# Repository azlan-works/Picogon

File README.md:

# Picogon
The Picogon in an opensource RP2354A based board for compact embedded applications. Designed as a host platform to integrate with more complex use cases, with peripherals attachable via exposed ENIG pads that connect to spring contacts on a compatible daughterboard. 

## Features:

- USB-C PD/PPS (3.3V to 24V)
- Battery management (3.7V LiPo)
- WiFi/BLE (2.4GHz built-in antenna)
- LoRa (SX1262 868-915MHz UFL connector)
- 9-axis DoF (IMU + Magnetometer)
- QWIIC/Stemma I2C port

  ## Notes:
  Currently untested

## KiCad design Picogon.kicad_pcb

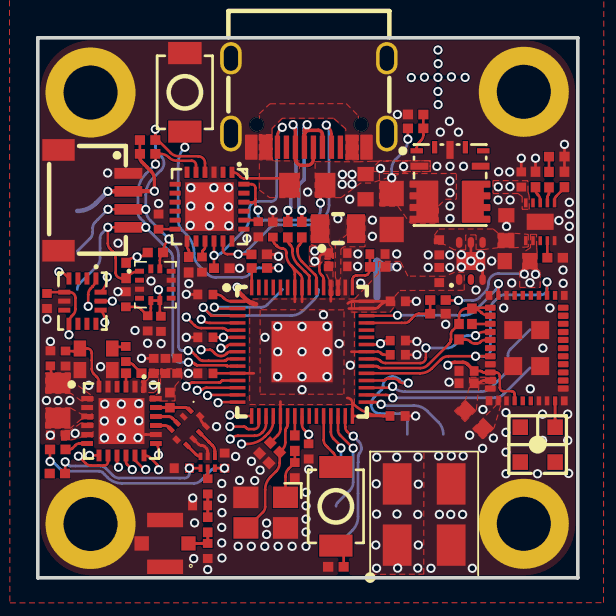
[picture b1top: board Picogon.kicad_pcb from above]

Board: 6 copper layers, 30.0 x 30.0 mm, 100 parts (0 on the bottom side), 75 nets.

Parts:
AE1: 47948-0001; ANT-SMD_47948-0001
C1, C11, C21, C22: 4.7uF; C0402
C2, C3, C4, C5, C6, C7, C8, C9, C10, C26, C27, C29, C30, C31, C33, C36, C37: 100nF; C0402
C12, C13: 4.7uF; C0402_WIDE
C14, C15: 15pF; C0402
C16: 47uF; C0805
C17: 10uF; C0603
C18: 10uF; C0402
C19, C23: 22uF; C0603
C20, C24, C25, C28, C35: 1uF; C0402
C32: 10pF; C0402
C34: 470nF; C0402
C38: 47pF; C0402
C39: 39pF; C0402
C40, C41: 33pF; C0402
C42, C43: 3.9pF; C0402
CN1: QWIIC; CONN-SMD_4P-P1.00_SM04B-SRSS-TB-LF-SN
L1: 3.3uH; IND-SMD_L2.0-W1.6_AOTA-B201610S3R3-101-T
L2: 2.2uH; L0603
L3: 10uH; L0805
L4: 47nH; L0402
L5: 9.1nH; L0402
M1, M2, M3, M4: M3_Hole
M5: 0900FM15K0039001E; FILTER-SMD_10P-L2.0-W1.3-BL
R1: 33Ω; R0402
R2, R3, R6: 1kΩ; R0402
R4, R5: 27Ω; R0402
R7, R10, R13, R16, R17, R20, R21: 10kΩ; R0402
R8, R9, R26, R27: 4.7kΩ; R0402
R11: 470Ω; R0402
R12: 1.5kΩ; R0402
R14: 3.3kΩ; R0402
R15, R18: 220Ω; R0402
R19, R29: 100Ω; R0402
R22: 10mΩ; R0805
R23, R24: 5.1kΩ; R0402
R25: 10kΩ; R0402
R28: FM8625H; DFN-6_L1.1-W0.7-P0.40-BL
SW1, SW2: Button; SW-SMD_L3.9-W3.0-P4.45
TCXO1: 32MHz; OSC-SMD_4P-L2.0-W1.6-BL_1XXD
U1: RP2354A; QFN-60_L7.0-W7.0-P0.40-TL-EP3.4
U2: ABM8-272-T3; CRYSTAL-SMD_4P-L3.2-W2.5-BL
U3: TPSM84209RKHR; QFN-9_L4.5-W4.0_TPSM84209RKHR
U4: ICM-42688-P; LGA-14_L3.0-W2.5-P0.50-TL
U5: LBEE5KL1YN-814; LGA-46_L7.0-W5.2_LBEE5KL1DX-883
U6: BQ25185DLHR; WSON-10_L2.2-W2.0-P0.40-BL-EP_TI_DLH0010A
U7: TLV76733DRVR; WSON-6_L2.0-W2.0-P0.65-TL-EP
U8: AP33772DKZ-13; QFN-24_L4.0-W4.0-P0.50-TL-EP2.7
U9: LIS3MDLTR; LGA-12_L2.0-W2.0-P0.50-BL
U10: SX1262IMLTRT; QFN-24_L4.0-W4.0-P0.50-BL-EP2.6
U11: IPEX-1; IPEX-SMD_4P-L2.6-W2.6-LS3.0
U12: 009296002202906; CONN-SMD_009296002202906
USBC1: USB-C 16P; USB-C_SMD-TYPE-C-31-M-12_1

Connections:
+1V1: C1.2, C2.2, C3.2, C13.2, L1.2, U1.6 (DVDD), U1.23 (DVDD), U1.39 (DVDD), U1.50 (VREG_FB)
+3V3: C4.2, C5.2, C6.2, C7.2, C8.2, C9.2, C10.2, C12.2, C20.2, C21.2, C25.2, C29.2, C30.2, C31.2, C35.2, C36.2, CN1.2 (VCC), R1.1, R8.2, R9.2, R26.2, R27.2, U1.1 (IOVDD), U1.11 (IOVDD), U1.20 (IOVDD), U1.30 (IOVDD), U1.38 (IOVDD), U1.44 (ADC_AVDD), U1.45 (IOVDD), U1.49 (VREG_VIN), U1.53 (USB_OTP_VDD), U1.54 (QSPI_IOVDD), U4.5 (VDDIO), U4.8 (VDD), U5.30 (VBAT), U5.36 (VIO), U7.1 (OUT), U9.5 (Vdd), U9.6 (Vdd_IO), U10.1 (VDD_IN), U10.10 (VBAT), U10.11 (VBAT_IO)
+BATT: C23.2, R20.2, U6.2 (BAT), U12.1
/Power/BAT_ADC: R20.1, R21.2, U1.42 (GPIO28_ADC2)
/Power/CC1: R23.2, U8.17 (CC1), USBC1.A5 (CC1)
/Power/CC2: R24.2, U8.16 (CC2), USBC1.B5 (CC2)
/Power/D+: R4.2, USBC1.A6 (DP1), USBC1.B6 (DP2)
/Power/D-: R5.2, USBC1.A7 (DN1), USBC1.B7 (DN2)
/Power/PD_SCL: CN1.4 (SCL), R9.1, R27.1, U1.10 (GPIO7), U8.5 (SCL), U9.1 (SCL/SPC)
/Power/PD_SDA: CN1.3 (SDA), R8.1, R26.1, U1.9 (GPIO6), U8.4 (SDA), U9.11 (SDA/SDI/SDO)
/RP2354A/GPIO2: U1.4 (GPIO2), U4.13 (AP_SCL/AP_SCLK)
/RP2354A/GPIO3: U1.5 (GPIO3), U4.14 (AP_SDA/AP_SDIO/AP_SDI)
/RP2354A/GPIO4: U1.7 (GPIO4), U4.1 (AP_SDO/AP_AD0)
/RP2354A/GPIO5: U1.8 (GPIO5), U4.12 (AP_CS)
/RP2354A/GPIO8: U1.12 (GPIO8), U4.4 (INT1/INT)
/RP2354A/GPIO9: U1.13 (GPIO9), U10.19 (NSS)
/RP2354A/GPIO10: U1.14 (GPIO10), U10.18 (SCK)
/RP2354A/GPIO11: U1.15 (GPIO11), U10.17 (MOSI)
/RP2354A/GPIO12: U1.16 (GPIO12), U10.16 (MISO)
/RP2354A/GPIO13: U1.17 (GPIO13), U10.15 (NRESET)
/RP2354A/GPIO14: U1.18 (GPIO14), U10.13 (DIO1)
/RP2354A/GPIO15: U1.19 (GPIO15), U10.14 (BUSY)
/RP2354A/GPIO23: U1.35 (GPIO23), U5.14 (BT_REG_ON), U5.28 (WL_REG_ON)
/RP2354A/GPIO24: R10.2, R11.2, U1.36 (GPIO24), U5.22 (SDIO_CMD), U5.23 (SDIO_DATA_2)
/RP2354A/GPIO25: U1.37 (GPIO25), U5.25 (SDIO_DATA_3)
/RP2354A/GPIO29_ADC3: U1.43 (GPIO29_ADC3), U5.20 (SDIO_CLK)
/RP2354A/XIN: C15.1, U1.21 (XIN), U2.3
/RP2354A/XOUT: R2.2, U1.22 (XOUT)
/Wireless/DIO2: R19.1, U10.12 (DIO2)
/Wireless/DIO3: C33.2, TCXO1.4 (VCC), U10.6 (DIO3)
GND: C1.1, C2.1, C3.1, C4.1, C5.1, C6.1, C7.1, C8.1, C9.1, C10.1, C11.1, C12.1, C13.1, C14.2, C15.2, C16.1, C17.1, C18.1, C19.1, C20.1, C21.1, C22.1, C23.1, C24.1, C25.1, C26.1, C27.1, C28.1, C29.1, C30.1, C31.1, C33.1, C34.1, C35.1, C36.1, C37.1, C38.1, C40.2, C41.1, C42.1, C43.1, CN1.1 (GND), CN1.5, CN1.6, M1.1 (1_1), M2.1 (1_1), M3.1 (1_1), M4.1 (1_1), M5.2 (GND), M5.5 (GND), M5.7 (GND), M5.9 (GND), M5.10 (GND), R3.1, R12.1, R14.2, R15.2, R16.2, R17.1, R21.1, R23.1, R24.1, R25.1, R28.2 (GND), SW1.1, TCXO1.1 (GND), TCXO1.2 (GND), U1.47 (VREG_PGND), U1.61 (EP), U2.2 (GND), U2.4 (GND), U3.8 (GND), U4.6 (GND), U5.1 (GND), U5.12 (GND), U5.19 (GND), U5.21 (GND), U5.29 (GND), U5.32 (GND(SR_PVSS)), U5.33 (GND(SR_PVSS)), U5.35 (GND), U5.39 (BT_DEV_WAKE), U5.40 (GND), U5.42 (GND), U5.43 (GND), U5.44 (GND), U5.45 (GND), U5.46 (GND), U6.5 (GND), U6.11 (EP), U7.3 (GND), U7.5 (GND), U7.7 (EP), U8.3 (GND), U8.25 (EP), U9.3 (GND), U9.9 (SD0/SA1), U10.2 (GND), U10.5 (GND), U10.8 (GND), U10.20 (GND), U10.25 (GND), U11.1, U11.2, U11.3, U12.2, USBC1.1 (EH), USBC1.2 (EH), USBC1.3 (EH), USBC1.4 (EH), USBC1.A1B12 (GND), USBC1.B1A12 (GND)
unnamed: C14.1, R2.1, U2.1
unnamed: C32.2, R18.1
unnamed: C39.2, C42.2, L5.2
unnamed: M5.3 (RFI_N), U10.22 (RFI_N)
unnamed: M5.4 (RFI_P), U10.21 (RFI_P)
unnamed: L4.1, M5.1 (RFO/VR_PA), U10.23 (RFO)
unnamed: M5.6 (SW_RFI), R28.3 (RF1)
unnamed: M5.8 (SW_RFO), R28.1 (RF2)
unnamed: R3.2, SW2.1
unnamed: R6.1, SW1.2
unnamed: R13.2, R14.1
unnamed: C39.1, R28.5 (AND)
unnamed: C40.1, R19.2, R28.6 (VCTL)
unnamed: C41.2, R28.4 (VDD), R29.2
unnamed: C32.1, TCXO1.3 (Output)
unnamed: R6.2, U1.60 (QSPI_SS)
unnamed: SW2.2, U1.26 (RUN)
unnamed: R5.1, U1.51 (USB_DM)
unnamed: R4.1, U1.52 (USB_DP)
unnamed: C11.2, R1.2, U1.46 (VREG_AVDD)
unnamed: L1.1, U1.48 (VREG_LX)
unnamed: R7.2, R12.2, U3.1 (FB)
unnamed: AE1.3 (3_3), U5.41 (ANT)
unnamed: R11.1, U5.24 (SDIO_DATA_0)
unnamed: R10.1, U5.26 (SDIO_DATA_1)
unnamed: L2.2, U5.34 (SR_VLX)
unnamed: C22.2, L2.1, U5.31 (VIN_LDO)
unnamed: R13.1, U6.7 (ILIM/VSET)
unnamed: R15.1, U6.8 (ISET)
unnamed: R16.1, U6.6 (TS/MR)
unnamed: R17.2, U6.4 (~CE)
unnamed: C26.2, U8.15 (IFB)
unnamed: R25.2, U8.13 (OTP)
unnamed: C27.2, U8.12 (V3VD)
unnamed: C28.2, U8.20 (V5V)
unnamed: L3.1, U10.9 (DCC_SW)
unnamed: C34.2, L3.2, U10.7 (VREG)
unnamed: C37.2, C38.2, L4.2, U10.24 (VR_PA)
unnamed: R18.2, U10.3 (XTA)
unnamed: C43.2, L5.1, U11.4 (ANT)
VBUS: C17.2, R22.2, U3.2 (VIN), U8.22 (VBUS), U8.24 (VCC)
VBUS_C: R22.1, U8.1 (ISENP), USBC1.A4B9 (VBUS), USBC1.B4A9 (VBUS)
VCHG: C16.2, C18.2, R7.1, U3.3 (VOUT), U6.10 (IN)
VSYS: C19.2, C24.2, U6.1 (SYS), U7.4 (EN), U7.6 (IN)
